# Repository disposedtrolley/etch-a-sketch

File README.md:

# etch-a-sketch

STM32-based Etch A Sketch widget with an OLED display and rotary encoders.

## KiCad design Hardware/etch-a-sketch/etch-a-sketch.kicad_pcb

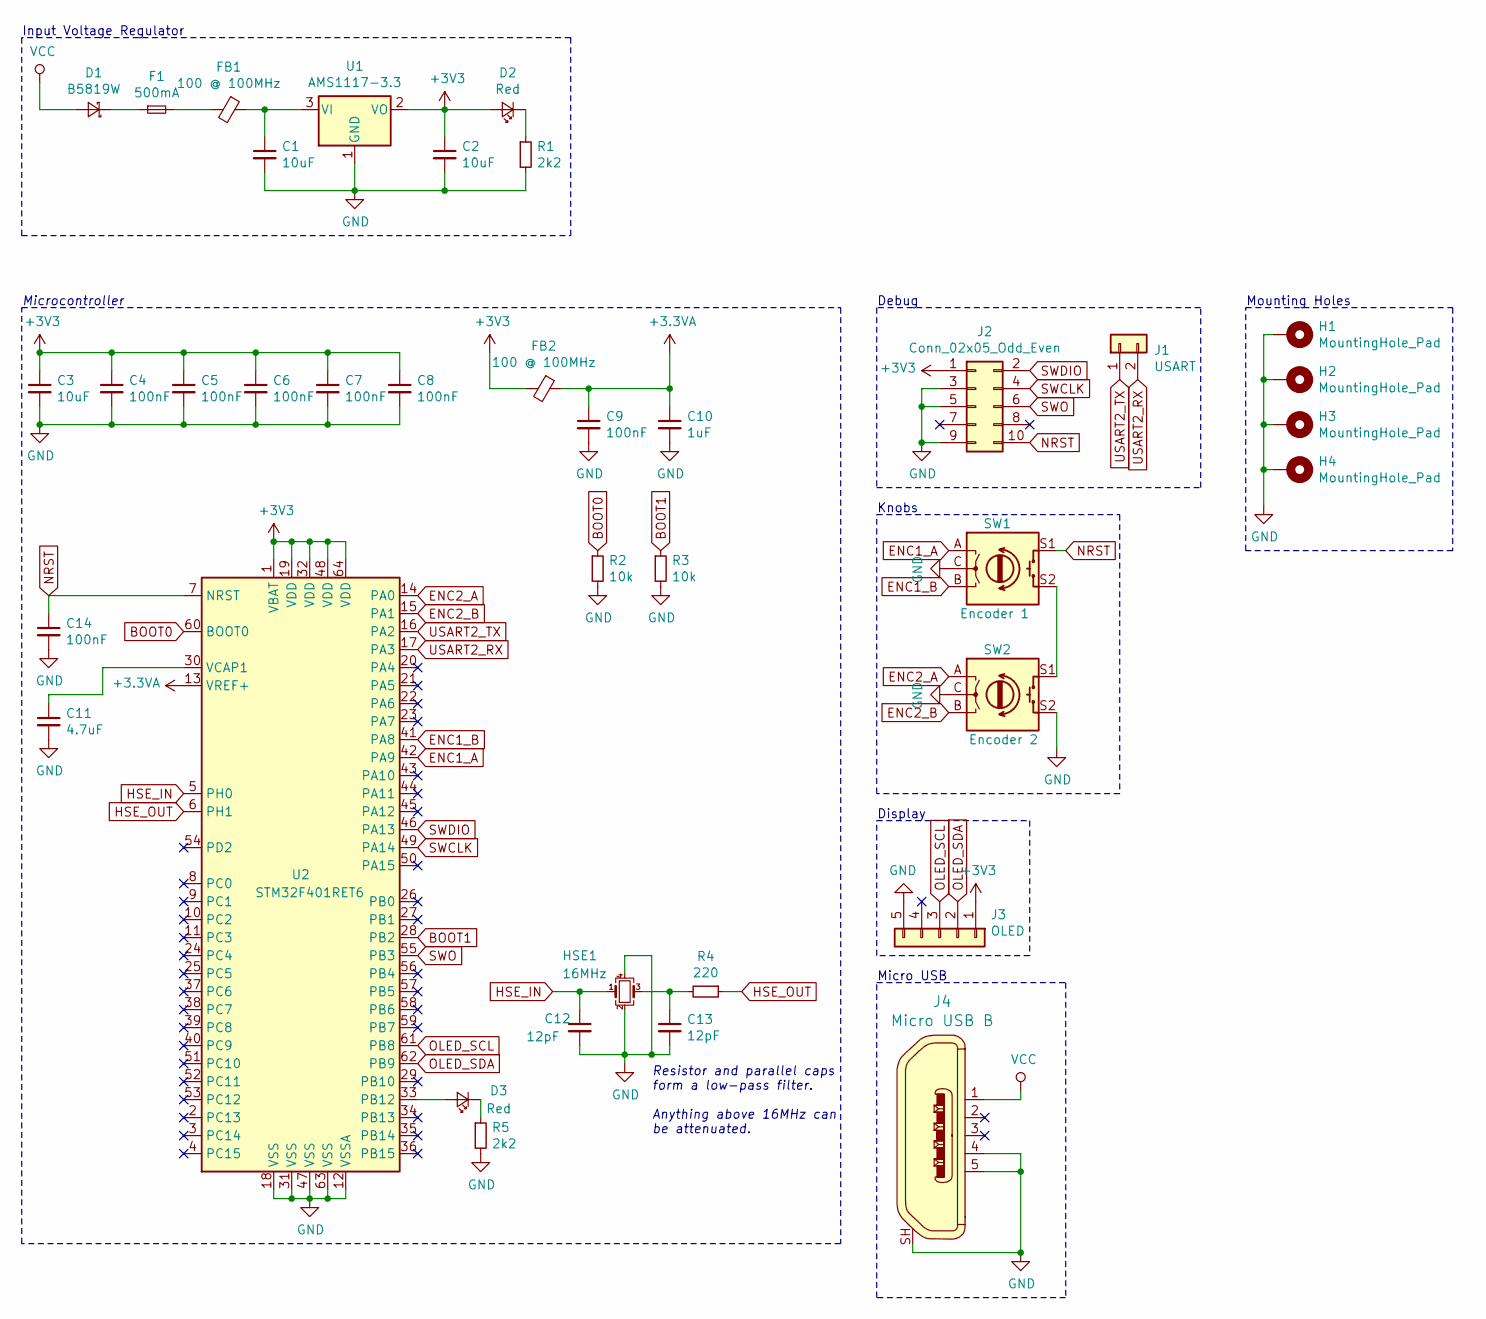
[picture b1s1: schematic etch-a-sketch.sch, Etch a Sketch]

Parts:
C1, C2: 10uF; C_0805_2012Metric
C3: 10uF; C_0603_1608Metric
C4, C5, C6, C7, C8, C9, C14: 100nF; C_0402_1005Metric
C10: 1uF; C_0402_1005Metric
C11: 4.7uF; C_0603_1608Metric
C12, C13: 12pF; C_0402_1005Metric
D1: B5819W; D_SOD-123
D2, D3: Red; LED_0603_1608Metric
F1: 500mA; Fuse_1206_3216Metric
FB1, FB2: 100 @ 100MHz; L_0805_2012Metric
H1, H2, H3, H4: MountingHole_Pad; MountingHole_4.3mm_M4_Pad_Via
HSE1: 16MHz; Crystal_SMD_3225-4Pin_3.2x2.5mm
J1: USART; PinSocket_1x02_P2.54mm_Vertical
J2: Conn_02x05_Odd_Even; PinHeader_2x05_P1.27mm_Vertical
J3: OLED; PinSocket_1x05_P2.54mm_Vertical
J4: Micro USB B; USB_Micro_B_Female_10118194-0001LF; MPN 10118194-0001LF; Digi-Key_PN 609-4618-1-ND
R1, R5: 2k2; R_0603_1608Metric
R2, R3: 10k; R_0402_1005Metric
R4: 220; R_0402_1005Metric
SW1: Encoder 1; RotaryEncoder_Alps_EC11E-Switch_Vertical_H20mm
SW2: Encoder 2; RotaryEncoder_Alps_EC11E-Switch_Vertical_H20mm
U1: AMS1117-3.3; SOT-223-3_TabPin2
U2: STM32F401RET6; LQFP-64_10x10mm_P0.5mm

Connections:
+3.3VA: C9.1, C10.1, FB2.1, U2.13 (VREF+)
+3V3: C2.1, C3.1, C4.1, C5.1, C6.1, C7.1, C8.1, D2.2 (A), FB2.2, J2.1, J3.1, U1.2 (VO), U2.1 (VBAT), U2.19 (VDD), U2.32 (VDD), U2.48 (VDD), U2.64 (VDD)
BOOT0: R2.1, U2.60 (BOOT0)
BOOT1: R3.1, U2.28 (PB2)
ENC1_A: SW1.A, U2.42 (PA9)
ENC1_B: SW1.B, U2.41 (PA8)
ENC2_A: SW2.A, U2.14 (PA0)
ENC2_B: SW2.B, U2.15 (PA1)
GND: C1.2, C2.2, C3.2, C4.2, C5.2, C6.2, C7.2, C8.2, C9.2, C10.2, C11.2, C12.2, C13.2, C14.2, H1.1, H2.1, H3.1, H4.1, HSE1.2, HSE1.4, J2.3, J2.5, J2.9, J3.5, J4.4, J4.5, J4.SH, R1.2, R2.2, R3.2, R5.2, SW1.C, SW2.C, SW2.S2, U1.1 (GND), U2.12 (VSSA), U2.18 (VSS), U2.31 (VSS), U2.47 (VSS), U2.63 (VSS)
HSE_IN: C12.1, HSE1.1, U2.5 (PH0)
HSE_OUT: R4.1, U2.6 (PH1)
NRST: C14.1, J2.10, SW1.S1, U2.7 (NRST)
unnamed: C1.1, FB1.1, U1.3 (VI)
unnamed: C11.1, U2.30 (VCAP1)
unnamed: C13.1, HSE1.3, R4.2
unnamed: D1.1 (K), F1.1
unnamed: D2.1 (K), R1.1
unnamed: D3.1 (K), R5.1
unnamed: D3.2 (A), U2.33 (PB12)
unnamed: F1.2, FB1.2
unnamed: SW1.S2, SW2.S1
OLED_SCL: J3.3, U2.61 (PB8)
OLED_SDA: J3.2, U2.62 (PB9)
SWCLK: J2.4, U2.49 (PA14)
SWDIO: J2.2, U2.46 (PA13)
SWO: J2.6, U2.55 (PB3)
USART2_RX: J1.2, U2.17 (PA3)
USART2_TX: J1.1, U2.16 (PA2)
VCC: D1.2 (A), J4.1

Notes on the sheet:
Input Voltage Regulator
Resistor and parallel caps form a low-pass filter. Anything above 16MHz can be attenuated.
Microcontroller
Debug
Display
Knobs
Mounting Holes
Micro USB

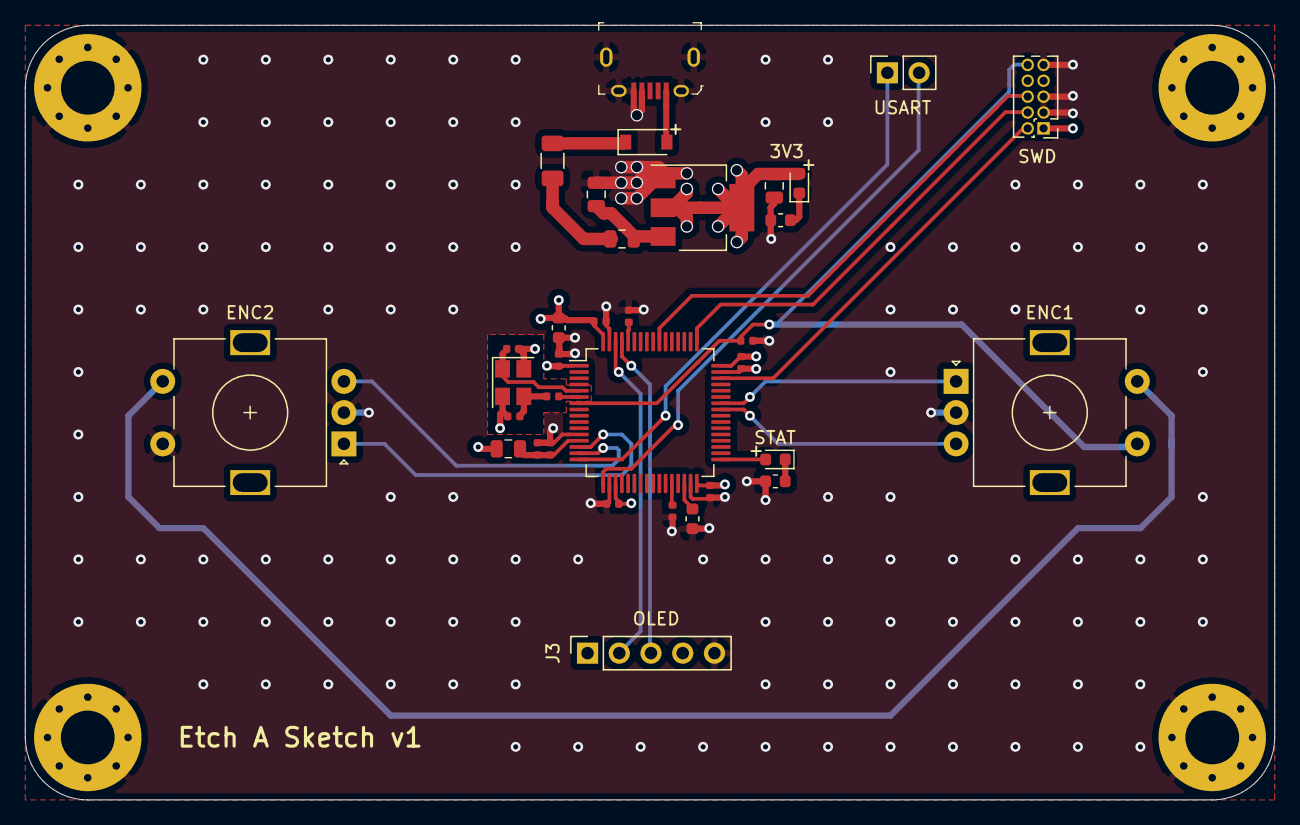
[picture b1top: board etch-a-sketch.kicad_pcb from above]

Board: 4 copper layers, 100.0 x 62.0 mm, 38 parts (0 on the bottom side), 29 nets.

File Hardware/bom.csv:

Designator,Quantity,Value,Footprint,LCSC Part #
"C1, C2, ",2,10uF,0805,C15850
"C3, ",1,10uF,0603,C19702
"C4, C5, C6, C7, C8, C9, C14, ",7,100nF,0402,C1525
"C10, ",1,1uF,0402,C52923
"C11, ",1,4.7uF,0603,C19666
"C12, C13, ",2,12pF,0402,C1547
"D1, ",1,B5819W,SOD-123,C8598
"D2, D3, ",2,Red,0603,C2286
"F1, ",1,500mA,1206,
"FB1, FB2, ",2,100 @ 100MHz,0805,C1015
"HSE1, ",1,16MHz,SMD-3225_4P,C13738
"J1, ",1,USART,Connector_PinSocket_2.54mm:PinSocket_1x02_P2.54mm_Vertical,
"J2, ",1,Conn_02x05_Odd_Even,Connector_PinHeader_1.27mm:PinHeader_2x05_P1.27mm_Vertical,
"J3, ",1,OLED,Connector_PinSocket_2.54mm:PinSocket_1x05_P2.54mm_Vertical,
"J4, ",1,Power Connector,10118194-0001LF,
"R1, R5, ",2,2k2,0603,C4190
"R2, R3, ",2,10k,0402,C25744
"R4, ",1,220,0402,C25091
"SW1, ",1,Encoder 1,Rotary_Encoder:RotaryEncoder_Alps_EC11E-Switch_Vertical_H20mm,
"SW2, ",1,Encoder 2,Rotary_Encoder:RotaryEncoder_Alps_EC11E-Switch_Vertical_H20mm,
"U1, ",1,AMS1117-3.3,SOT-223-3,C6186
"U2, ",1,STM32F401RET6,Package_QFP:LQFP-64_10x10mm_P0.5mm,C116978

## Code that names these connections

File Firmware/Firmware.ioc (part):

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Mcu.UserName=STM32F401RETx
PA14.GPIO_Label=TCK
PH1\ -\ OSC_OUT.Mode=HSE-External-Oscillator
PA9.GPIOParameters=GPIO_PuPd
boardIOC=true
PA9.GPIO_PuPd=GPIO_PULLUP
RCC.SYSCLKSource=RCC_SYSCLKSOURCE_PLLCLK
PA0-WKUP.Signal=S_TIM2_CH1_ETR
PA13.Signal=SYS_JTMS-SWDIO
PA3.Mode=Asynchronous
PH0\ -\ OSC_IN.Mode=HSE-External-Oscillator
PH0\ -\ OSC_IN.Signal=RCC_OSC_IN
PB9.Mode=I2C
PA9.Signal=S_TIM1_CH2
PB12.PinState=GPIO_PIN_SET
PA8.GPIOParameters=GPIO_PuPd
PA1.GPIO_PuPd=GPIO_PULLUP
PA1.Signal=S_TIM2_CH2
PA0-WKUP.GPIOParameters=GPIO_PuPd
RCC.HSE_VALUE=16000000
PH1\ -\ OSC_OUT.Signal=RCC_OSC_OUT
PB3.Mode=Trace_Asynchronous_SW
board=NUCLEO-F401RE
PA1.GPIOParameters=GPIO_PuPd
PA14.Mode=Trace_Asynchronous_SW
PB3.GPIOParameters=GPIO_Label
PA8.Signal=S_TIM1_CH1
PA13.Mode=Trace_Asynchronous_SW
Mcu.Name=STM32F401R(D-E)Tx
PA2.Signal=USART2_TX
PA13.GPIO_Label=TMS
PA13.GPIOParameters=GPIO_Label
PB3.Signal=SYS_JTDO-SWO
RCC.SYSCLKFreq_VALUE=84000000
Mcu.Package=LQFP64
PB9.Signal=I2C1_SDA
PA14.GPIOParameters=GPIO_Label
PA14.Signal=SYS_JTCK-SWCLK
PA8.GPIO_PuPd=GPIO_PULLUP
PB8.Mode=I2C
PA2.Mode=Asynchronous
PB8.Signal=I2C1_SCL
PA0-WKUP.GPIO_PuPd=GPIO_PULLUP
PB12.GPIOParameters=PinState
PB12.Signal=GPIO_Output
PA3.Signal=USART2_RX
PB3.GPIO_Label=SWO

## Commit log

2020-03-08 feat: redirect _write to uart2
2020-03-08 wip: working state
    This commit brings the encoder value reading to a working state, however
    it uses a combination of GUI setup (generated code) and custom setup
    logic to properly configure and initialise the GPIO pins and Timer
    peripheral to work correctly with a rotary encoder.
    The setup logic should be moved exclusively into user code so nothing
    important becomes buried.
2020-03-09 refactor: change encoder mode to TI1
    Seems to work fine with one channel. Detects direction and also means
    the count only needs to be divided by 2 instead of 4.
2020-03-09 feat: configure GPIO via code, start timer using the HAL method
2020-03-09 feat: divide count by 2, get dir from CR1, print both
2020-03-09 chore: format code
2020-03-13 feat: add epaper lib and example
2020-03-14 refactor: restructure epaper libs
2020-03-14 feat: re-enable USART, move DC and BUSY pins
2020-03-14 chore: remove CN resources
2020-03-14 refactor: add and use #defines for commands
2020-03-14 chore: remove header noise, add LICENSE
2020-03-14 fix: use hex in LUT arrays
2020-03-14 chore: remove redundant comments
2020-03-15 refactor: configure TIM1 via UI
2020-03-15 feat: set encoder to trigger an interrupt
2020-03-15 feat: animate line
2020-03-21 regenerate .ioc as cmake project
2020-03-21 add epaper deps and old main.c
2020-03-21 chore: add gitignore, include `.idea` and `cmake-build-debug`
2020-03-21 docs: add readme
2020-03-21 feat/refactor: add epaper deps to CMakeLists template, move epaper animation into func
2020-03-21 feat: animate in infinite loop instead
2020-03-21 fix: move global vars into user code block
2020-03-21 feat: add direction, draw only when rotary encoder has been turned
2020-03-28 feat: remove epaper dependencies and SPI config
2020-03-28 feat: add I2C config and OLED driver lib
2020-03-28 feat: remove #defines in lib to force I2C, add lib to include dirs, run tests
2020-03-28 fix: use correct multiplex and offset values
2020-03-29 feat: fix and configure ssd1306 lib for 128px high displays
2020-03-29 feat: draw on x-axis when encoder is turned
2020-03-29 feat: enable TIM3 for second rotary encoder
2020-03-29 refactor: remove `prevX` and `prevY` globals
2020-04-13 feat: initial attempt
2020-04-13 feat: redo main schematic design
2020-04-13 feat: add OLED and encoders
2020-04-13 feat: add status LED to PB12
2020-04-13 feat: add power LED
2020-04-13 feat: organise schematic into blocks
2020-04-13 feat: add USART to PA2 and PA3, change OLED to generic connector
2020-04-13 feat: add micro USB connector
2020-04-13 fix: micro USB should provide VCC in
2020-04-13 feat: assign all footprints
2020-04-13 feat: generate netlist
2020-04-13 feat: add PCB outline and import netlist
2020-04-13 feat: position mounting holes
2020-04-13 feat: add rounded corners to PCB outline
2020-04-13 fix: resize PCB outline to be 62mm tall
2020-04-13 feat: move MCU to centre of board
2020-04-13 feat: associate correct footprint for OLED connector
2020-04-13 fix: actually maybe better to keep the OLED socketed
2020-04-13 feat: place HSE
2020-04-13 feat: add decoupling capacitors
2020-04-14 feat: place encoders, refine placement of power regulator
2020-04-14 feat: place OLED socket
2020-04-14 feat: place debug connectors and resistor for power regulator
2020-04-14 feat: place status LED
2020-04-14 feat: finalise layout
2020-04-14 refactor: reposition encoders
    - Move ENC2 to use PA0 and PA2 so they don't need to cross to the other
    side of the MCU.
    - Swap ENC1's A and B pins so they don't cross each other.
2020-04-17 feat: configure board
2020-04-17 feat: add GND and 3v3 fills to all layers
2020-04-17 feat: route oscillator and refine fills
2020-04-17 feat: add small trace between osc fill and In1.Cu full
2020-04-17 feat: route power
2020-04-17 feat: complete initial routing
2020-04-18 feat: add silkscreen labels
2020-04-18 feat: add labels for power, status LED, and connectors
2020-04-18 feat: add polarity and pin 1 markers
2020-04-18 refactor: refine ground fill for oscillator
2020-04-18 feat: add title
2020-04-18 feat: move USART to top, rearrange encoder 2 pins
2020-04-18 fix: swap encoder labels
2020-04-18 refactor: place title on bottom-left
2020-04-18 fix: connect oscillator ground plane to ground
2020-04-18 feat: add via stitching
2020-04-18 docs: update README with pcb render
2020-04-18 fix: enable back layers, clean up USB ground traces
2020-04-18 feat: generate gerbers, BOM, and position files
2020-04-18 fix: adjust orientation of MCU and voltage regulator
2020-04-18 feat: change micro USB footprint to 10118194
2020-04-18 feat: adjust connector position according to datasheet
2020-04-18 feat: route connector pins
2020-04-18 feat: update position and overall BOM
2020-04-18 feat: update gerbers
2020-04-18 fix: wrong rotations
2020-04-18 feat: change SWD connector to through-hole
2020-04-18 feat: update pos and overall BOM
2020-04-18 feat: regenerate drill and gerbers
2020-04-18 fix: correct rotation of MCU and voltage regulator
2020-04-18 feat: add polarity for schottky diode, move pin marker for USB port
2020-04-19 feat: connect encoder switches to act as NRST button
2020-04-19 feat: route encoder buttons to NRST, add decoupling capacitor
2020-04-19 refactor: shorten route of ENC2 A and B
2020-04-19 feat: update gerbers, drill, BOM, and position files
2020-04-19 refactor: move NRST decoupling capacitor close to MCU
2020-04-19 feat: update PCB render
2020-05-02 feat: move ENC_2 to PA0 and PA1
2020-05-02 feat: enable HSE
2020-05-02 feat: disable pushbutton pin
2020-05-02 fix: HSE clock, TIM2 for encoder, PB12 for status LED
